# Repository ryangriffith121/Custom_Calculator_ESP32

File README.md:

# Custom Calculator ESP32

A custom calculator project built around an ESP32 microcontroller and a 4-inch ST7796S TFT display. The PCB and schematic have been developed in KiCad, and the next phase is generating Gerber files for manufacturing, followed by enclosure design and firmware development.

## 🎯 Project Goal

Create a compact, custom 4-function calculator with:

- Addition
- Subtraction
- Multiplication
- Division

The design combines a tactile keypad matrix, a high-visibility graphics display, and a lightweight ESP32-based control system.

## 🧩 Hardware Overview

### Core controller
- ESP32 development module / ESP32-WROOM-style board footprint
- Connected to the keypad matrix and display interface
- Planned for calculation logic, UI rendering, and input handling

### Display
- 4-inch TFT display
- ST7796S controller
- Intended for calculator UI, numeric input, operator selection, and result display

### Input device
- Tactile switch matrix arranged in a key layout
- Supports numeric keys and operator keys
- Wiring is organized in a row/column matrix for efficient GPIO usage

### Power and support
- 3.3V logic rail
- Test points for power, reset, SPI, and signal debug
- ESP32 GPIOs mapped for display and keypad interfacing

## ✅ Current Status

### Completed
- PCB design completed in KiCad
- Schematic capture completed in KiCad
- Gerber files generated and ready for manufacturing
- Device planning for ESP32 + display + keypad matrix
- GPIO and pin allocation for the external interfaces
- Basic project structure in the workspace

Schematic:

PCB Layout and Wiring:

PCB Rendering:

### Remaining work
- Enclosure design and mechanical fit for the display, buttons, and assembly
- Firmware programming for keypad scanning, display output, and calculator logic
- Final validation and hardware bring-up

## 📁 Repository Structure

```text
Custom_Calculator_ESP32/
├── CAD/
│   └── (mechanical / enclosure or enclosure-related files)
├── ECAD/
│   └── Calculator/
│       ├── Calculator.kicad_pro
│       ├── Calculator.kicad_sch
│       ├── Calculator.kicad_pcb
│       └── Calculator.kicad_prl
├── Programming/
│   └── (firmware source code and future development files)
├── README.md
└── .git/
```

## 📝 Design Notes

This project is intended to be a functional calculator rather than a general-purpose embedded display demo. The hardware is being designed around a straightforward architecture:

1. User presses keypad buttons.
2. ESP32 reads the matrix input.
3. Firmware interprets numeric and operator inputs.
4. Calculation result is rendered on the ST7796S display.

## 🚀 Planned Next Steps

- Design the enclosure to match the completed PCB and display layout
- Add silkscreen labeling and mechanical constraints
- Complete firmware programming for keypad scanning, display rendering, and calculator logic
- Validate the display graphics and UI flow on the physical hardware
- Finalize assembly and testing of the completed calculator

## 💻 Firmware Direction

The firmware can be implemented with:

- GPIO scanning for the keypad matrix
- SPI communication to the ST7796S TFT display
- Basic arithmetic state machine for calculator operation
- Keyboard debounce handling
- Result and expression rendering on screen

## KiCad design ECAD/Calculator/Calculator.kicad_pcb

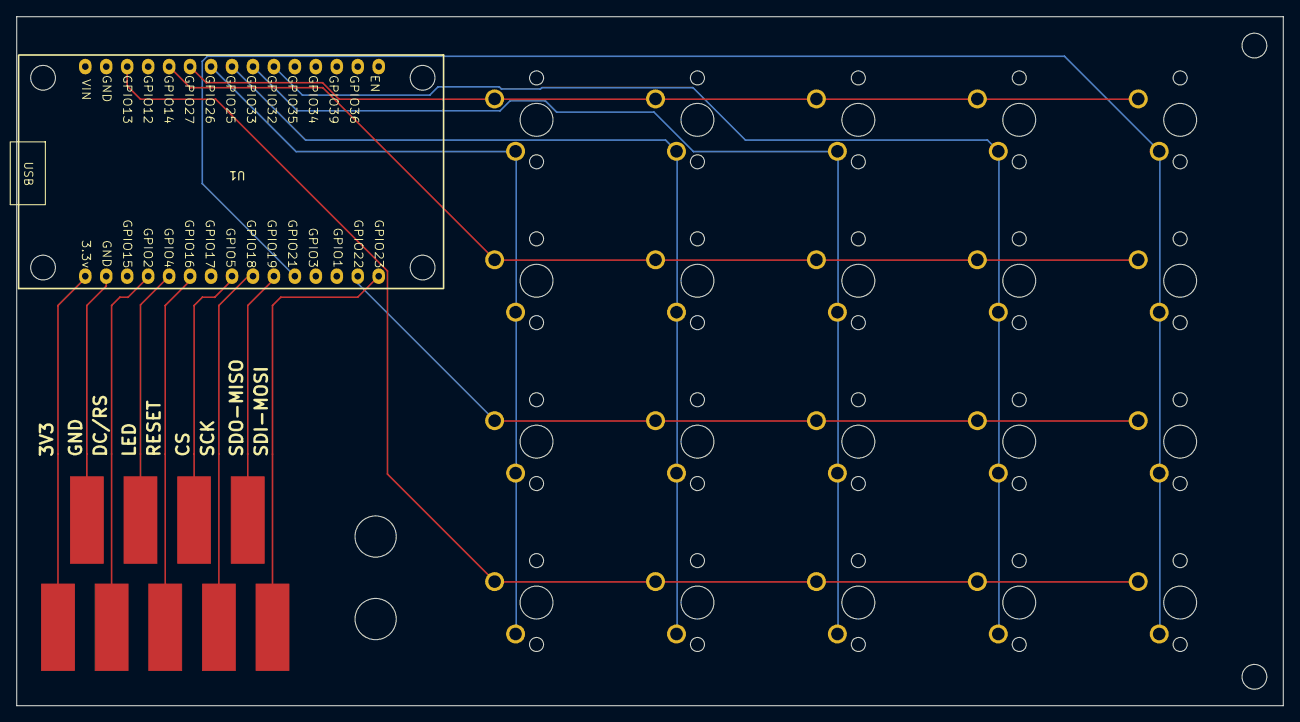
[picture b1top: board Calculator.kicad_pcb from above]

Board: 2 copper layers, 153.5 x 83.5 mm, 30 parts (0 on the bottom side), 9 nets.

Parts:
SW1, SW2, SW3, SW4, SW5, SW6, SW7, SW8, SW9, SW10, SW11, SW12, SW13, SW14, SW15, SW16, SW17, SW18, SW19, SW20: Switch_Tactile_ESwitch; MX-Solderable-1U
TP1, TP2, TP3, TP4, TP5, TP6, TP7, TP8, TP9: TestPoint; Solder_pad
U1: ESP32_30pin

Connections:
/Col 1: SW1.2, SW2.2, SW3.2, SW4.2, SW5.2, U1.3 (GPIO13)
/Col 2: SW6.2, SW7.2, SW8.2, SW9.2, SW10.2, U1.29 (GPIO22)
/Col 3: SW11.2, SW12.2, SW13.2, SW14.2, SW15.2, U1.5 (GPIO14)
/Col 4: SW16.2, SW17.2, SW18.2, SW19.2, SW20.2, U1.6 (GPIO27)
/Row A: SW1.1, SW6.1, SW11.1, SW16.1, U1.7 (GPIO26)
/Row B: SW2.1, SW7.1, SW12.1, SW17.1, U1.8 (GPIO25)
/Row C: SW3.1, SW8.1, SW13.1, SW18.1, U1.9 (GPIO33)
/Row D: SW4.1, SW9.1, SW14.1, SW19.1, U1.10 (GPIO32)
/Row E: SW5.1, SW10.1, SW15.1, SW20.1, U1.26 (GPIO21)
